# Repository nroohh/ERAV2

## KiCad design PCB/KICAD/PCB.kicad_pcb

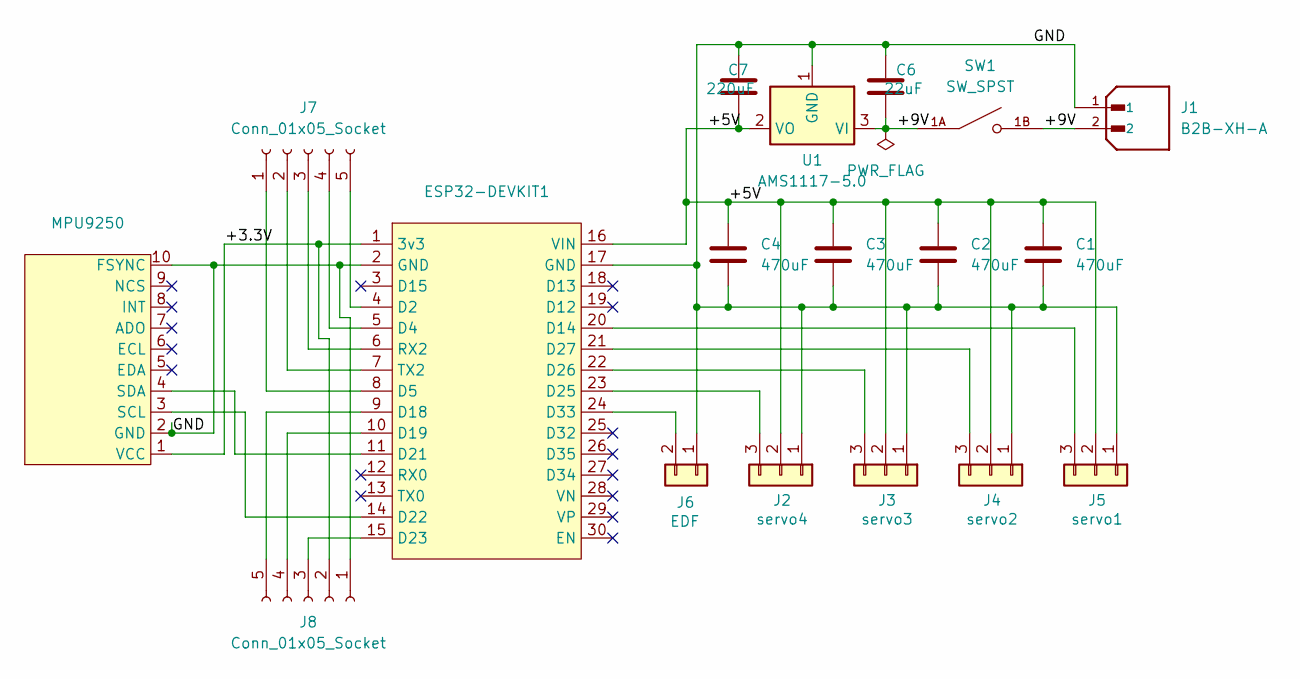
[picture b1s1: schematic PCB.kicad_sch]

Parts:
C1, C2, C3, C4: 470uF; CAP_YX_8X11P5_RUB
C6: 22uF; CAP_PAN_5X11_PAN
C7: 220uF; CAP_PAN_6.3X11.2_PAN
ESP32-DEVKIT1: ESP32 DEVKIT V1
J1: B2B-XH-A; JST_XH_B2B-XH-A_1x02_P2.50mm_Vertical; PARTREV N/A
J2: servo4; PinHeader_1x03_P2.54mm_Vertical
J3: servo3; PinHeader_1x03_P2.54mm_Vertical
J4: servo2; PinHeader_1x03_P2.54mm_Vertical
J5: servo1; PinHeader_1x03_P2.54mm_Vertical
J6: EDF; PinHeader_1x02_P2.54mm_Vertical
J7, J8: Conn_01x05_Socket; PinHeader_1x05_P2.54mm_Vertical
MPU9250: MPU9250
SW1: SW_SPST; SW_DS01-254-L-01BE; PARTREV 1.0
U1: AMS1117-5.0; SOT-223-3_TabPin2

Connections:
/+3.3V: ESP32-DEVKIT1.1 (3v3), J8.2, MPU9250.1 (VCC)
/+5V: C1.1, C2.1, C3.1, C4.1, C7.1, ESP32-DEVKIT1.16 (VIN), J2.2, J3.2, J4.2, J5.2, U1.2 (VO)
/+9V: C6.1, J1.2, SW1.1A, SW1.1B, U1.3 (VI)
/GND: C1.2, C2.2, C3.2, C4.2, C6.2, C7.2, ESP32-DEVKIT1.2 (GND), ESP32-DEVKIT1.17 (GND), J1.1, J2.1, J3.1, J4.1, J5.1, J6.1, J8.1, MPU9250.2 (GND), MPU9250.10 (FSYNC), U1.1 (GND)
unnamed: ESP32-DEVKIT1.4 (D2), J7.5
unnamed: ESP32-DEVKIT1.5 (D4), J7.4
unnamed: ESP32-DEVKIT1.8 (D5), J7.1
unnamed: ESP32-DEVKIT1.20 (D14), J5.3
unnamed: ESP32-DEVKIT1.9 (D18), J8.5
unnamed: ESP32-DEVKIT1.10 (D19), J8.4
unnamed: ESP32-DEVKIT1.11 (D21), MPU9250.4 (SDA)
unnamed: ESP32-DEVKIT1.14 (D22), MPU9250.3 (SCL)
unnamed: ESP32-DEVKIT1.15 (D23), J8.3
unnamed: ESP32-DEVKIT1.23 (D25), J2.3
unnamed: ESP32-DEVKIT1.22 (D26), J3.3
unnamed: ESP32-DEVKIT1.21 (D27), J4.3
unnamed: ESP32-DEVKIT1.24 (D33), J6.2
unnamed: ESP32-DEVKIT1.6 (RX2), J7.3
unnamed: ESP32-DEVKIT1.7 (TX2), J7.2

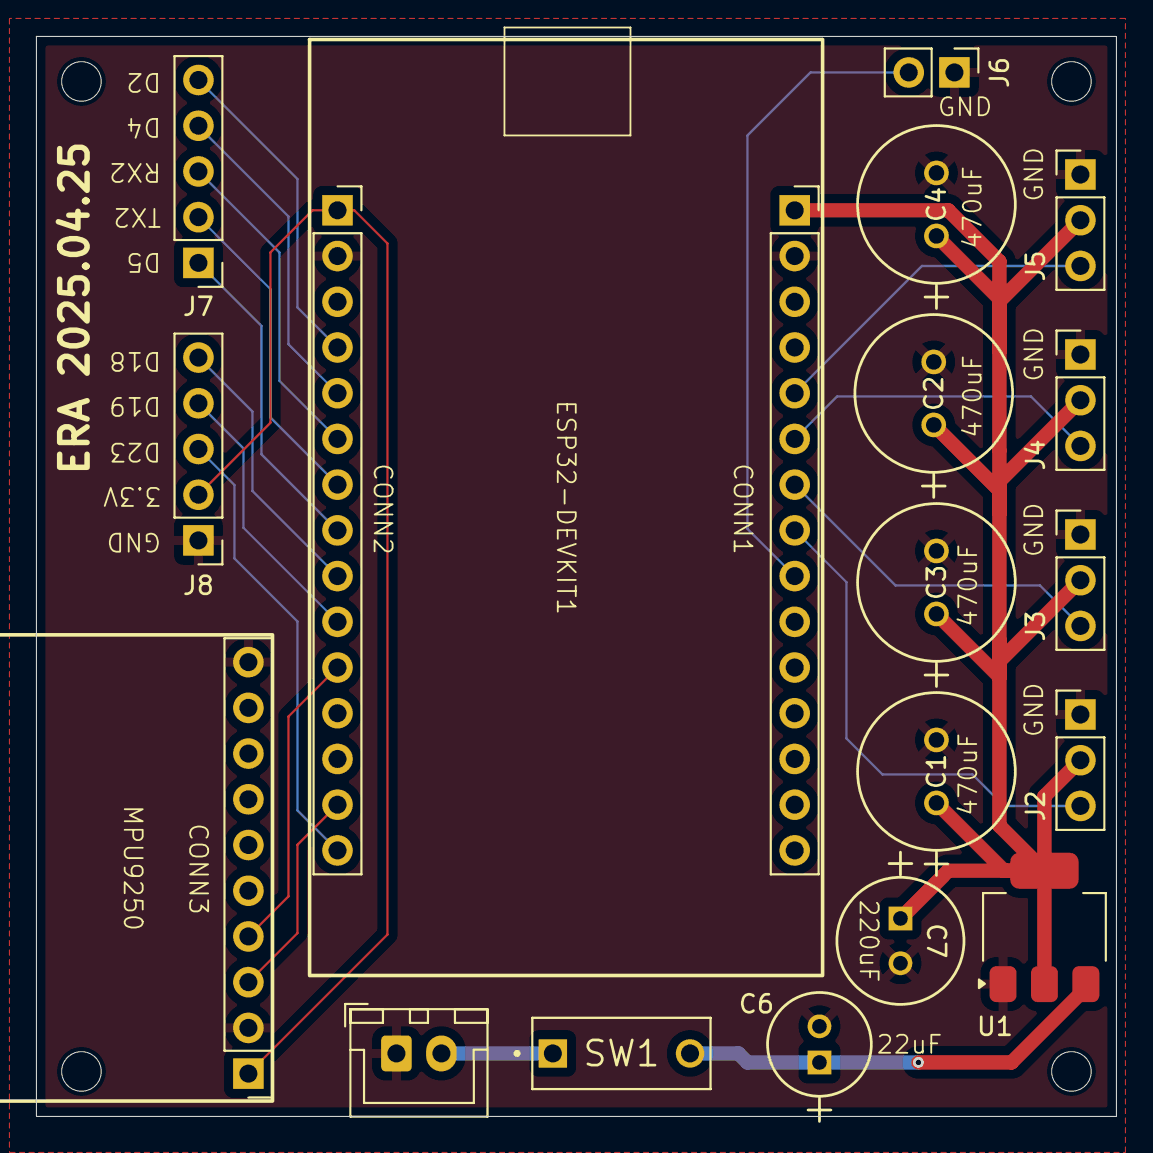
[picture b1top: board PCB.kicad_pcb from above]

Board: 2 copper layers, 60.0 x 60.0 mm, 18 parts (0 on the bottom side), 19 nets.

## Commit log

2025-12-02 init
2025-12-30 change made
